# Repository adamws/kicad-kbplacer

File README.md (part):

#  kicad-kbplacer

KiCad plugin for mechanical keyboard design. It features automatic key placement and routing
based on layout descriptions from [Keyboard Layout Editor NG](https://editor.keyboard-tools.xyz)
and [ergogen](https://github.com/ergogen/ergogen).

**Table of Contents**
- [Motivation](#motivation)
- [Features](#features)
- [Installation](#installation)
  - [As KiCad plugin](#installation-as-kicad-plugin)
  - [As python package](#installation-as-python-package)
- [Use from KiCad](#how-to-use-from-kicad)
  - [Options overview](#options-overview)
  - [Diode placement and routing](#diode-placement-and-routing)
    - [Diode automatic orientation adjustment](#diode-automatic-orientation-adjustment)
  - [Track templating](#track-templating)
    - [JSON presets](#json-presets)
  - [Additional elements placement](#additional-elements-placement)
  - [Building board outline](#building-board-outline)
  - [Run without layout](#run-without-layout)
- [Use from CLI or from another tools](#how-to-use-from-cli-or-another-tools)
  - [Run as a script](#run-as-a-script)
  - [Use in python projects](#use-in-python-projects)
- [Demo keyboard project](#demo-keyboard-project)
- [Troubleshooting](#troubleshooting)
  - [Plugin does not load](#plugin-does-not-load)
  - [Plugin misbehaves or crashes](#plugin-misbehaves-or-crashes)

<!-- TOC -->
## Motivation

All PCB's for mechanical keyboards shares common properties which creates great
opportunity for scripting. Although this project does not aim to provide
complete automatic PCB generation tool it speeds up development process
by reducing tedious element placement and routing tasks.

<!-- TOC -->
## Features

- Automatic keys and diodes placement
- Track routing and track template replication
- Support for KLE, [VIA](https://www.caniusevia.com/docs/layouts), [QMK](https://docs.qmk.fm/reference_info_json#layouts) and [ergogen](https://github.com/ergogen/ergogen) inputs
- User selectable diode position in relation to key position
- Configurable additional elements placement
- Board outline generation

> [!NOTE]
> KLE is a layout description format established by https://github.com/ijprest
> and used by https://www.keyboard-layout-editor.com/
>
> The [Keyboard Layout Editor NG](https://editor.keyboard-tools.xyz/) referenced in
> this documentation is a modernized re-implementation using same data format.

> [!WARNING]
> Ergogen support is new experimental feature and it has not been tested extensively

Some examples can be found in [examples](./examples) directory.

**See also:**

:link: [Keyboard PCB design with ergogen and kbplacer](https://adamws.github.io/keyboard-pcb-design-with-ergogen-and-kbplacer/)

<!-- TOC -->
## Installation

<!-- TOC -->
### As KiCad plugin

To install release version of this plugin, use KiCad's `Plugin and Content Manager`
and select `Keyboard footprints placer` from official plugin repository.

To install development version, see how to use [custom plugin repository](./docs/custom_repository.md).
Custom repository is automatically updated with latest `master` branch builds
and it is available [here](https://adamws.github.io/kicad-kbplacer).

For development activities, it is recommended to checkout this repository and copy (or link)
content of `kbplacer` directory to one of the KiCad's plugin search paths.
For more details see [this](https://dev-docs.kicad.org/en/apis-and-binding/pcbnew/) guide.

After installation, plugin can be started by clicking plugin icon on the toolbar:

or selecting it from `Tools -> External Plugins` menu.
For more details about plugin usage see [Use from KiCad](#how-to-use-from-kicad) section.

<!-- TOC -->
### As python package

The `kbplacer` can be installed with pip:

```shell
pip install kbplacer
```

When installed this way, it **can't** be launched from KiCad as KiCad plugin.
This option exist for usage via command line interface or for integrating with
another tools.

Command line interface provides more options but generally it is recommended for
more advanced users. For example it allows to create PCBs without schematic,
which is non-typical KiCad workflow.
For details see [Use from CLI or from another tools](#how-to-use-from-cli-or-another-tools) section.

> [!IMPORTANT]
> Most of the `kbplacer` python package functionalities depends on `pcbnew` package
> which is distributed as part of KiCad installation.
> This means, that on Windows it is **required** to use python bundled with KiCad.
> On Linux, `pcbnew` package should be available globally (this can be verified by
> running `python -c "import pcbnew; print(pcbnew.Version())"`) so it may not work
> inside isolated environment. To install inside virtual environment created with `venv`
> it is required to use `--system-site-package` option when creating this environment.

> [!NOTE]
> Both installation methods can be used simultaneously. When installed as KiCad plugin,
> some scripting capabilities are still available, but in order to use `kbplacer`
> in another python scripts, installing as python package is required.

<!-- TOC -->
## Use from KiCad

This is _traditional_ way of using this tool. Before it can be used on `kicad_pcb` project
file, user needs to create it and populate with footprints. In typical KiCad workflow
this is started by creating schematic. When PCB file is ready, user can start `kbplacer`
plugin in GUI mode from KiCad and run it with selected options.
To use this tool in this way, it needs to be installed following [plugin installation guide](#as-kicad-plugin).

- Create switch matrix schematic which meets following requirements:
  - Each switch has connected diode
    - Diodes can be connected in either direction. Track router attempts to connect
      closest (to each other) pads of switch and diode as long as both have same `netname`,
      i.e. are connected on the schematic
    - Each switch can have multiple diodes
  - Symbols are ordered by Y position.
      - :warning: This annotation scheme might not work well for certain 'ergo' layouts.
      - Annotation order is ignored when using layout with mapping to matrix defined
        (see [VIA](https://www.caniusevia.com/docs/layouts#switch-matrix-co-ordinates)
        specification).

    To learn more see [annotation guide](./docs/annotation_guide.md).

- Create new PCB and load netlist
- Obtain json layout file from [Keyboard Layout Editor NG](https://editor.keyboard-tools.xyz) or
  convert [ergogen](https://github.com/ergogen/ergogen) points file to json

  <details>
  <summary>Keyboard Layout Editor NG details <i>(click to expand)</i></summary>

    Plugin supports both raw and internal [kle-serial](https://github.com/ijprest/kle-serial) layout files
    and [via](https://www.caniusevia.com/docs/layouts) files.
    Detection of layout format will be done automatically.

    > [!NOTE]
    > When using `via` layouts, switch matrix **must** be annotated according to `via` rules.
    > If layout supports [multiple layout of keys](https://www.caniusevia.com/docs/layouts#layout-options)
    > only the default one will be used by `kicad-kbplacer`.

  </details>

  <details>
  <summary>ergogen details <i>(click to expand)</i></summary>

    - open your design in https://ergogen.xyz/ and enable `Debug` in options

    - download `points.yaml`

    - convert `yaml` to `json` (this operation is not integrated with `kicad-kbplacer` source
      because it would require installation of third-party `pyyaml` package and there is no
      good way to manage plugin dependencies yet)
      - you can use online converter, for example https://jsonformatter.org/yaml-to-json
    - converted file should be automatically recognized in next steps

  </details>

- Run `kicad-kbplacer` plugin
- Select json layout file and plugin options and click OK.

It is possible to run this plugin from command line. Everything which can be done via GUI can
be also achieved using command line.
Execute following command (in the directory where plugin is installed) to get more details:

```
python -m com_github_adamws_kicad-kbplacer --help
```

> [!IMPORTANT]
> On windows, use python bundled with KiCad

<!-- TOC -->
### Options overview

<table>
  <tr>
    <th align="center"><b>Section</b></th>
    <th align="center"><b>Label</b></th>
    <th align="center"><b>Description</b></th>
  </tr>
  <tr>
    <td rowspan="6" align="center" style="vertical-align: middle;">Switch settings</td>
    <td align="center" style="vertical-align: middle;">Keyboard Layout</td>
    <td>
      Layout file path or <a href="https://editor.keyboard-tools.xyz/">Keyboard Layout Editor NG</a>
      share link (<code>https://editor.keyboard-tools.xyz/#share=...</code>).
      Supports Keyboard Layout Editor NG
      json layouts in both raw and internal form, <a href="https://www.caniusevia.com/docs/layouts">via</a>
      and <a href="https://docs.qmk.fm/reference_info_json#layouts">qmk</a> json layouts and <a href="https://docs.ergogen.xyz/formats">ergogen</a>
      canonical yaml points files converted to json.</br>
      Can be empty to run without switch footprints placement.
    </td>
  </tr>
  <tr>
    <td align="center" style="vertical-align: middle;">Step X / Step Y</td>
    <td>
      Distance (in millimeters) of 1U between two switches in X and Y directions
      (defaults to <code>19.05</code>).</br>
      When selected layout file explicitly defines spacing in its metadata,
      these fields are updated with values from that file.
    </td>
  </tr>
  <tr>
    <td align="center" style="vertical-align: middle;">Footprint Annotation</td>
    <td>
      The switch footprint annotation format with single replacement field <code>{}</code>
      which will get replaced with incremented footprint number.
      This string is internally used by python's <code>str.format</code> function.
    </td>
  </tr>
  <tr>
    <td align="center" style="vertical-align: middle;">Start index</td>
    <td>
      Starting index used to match footprint annotations (default: 1).
      Controls which number to use when matching the first switch footprint.
      For example, with annotation format <code>SW{}</code> and start index <code>0</code>,
      the first switch will be <code>SW0</code> instead of <code>SW1</code>.
    </td>
  </tr>
  <tr>
    <td align="center" style="vertical-align: middle;">Orientation</td>
    <td>
      Angle (in degrees) of switch footprints.
    </td>
  </tr>
  <tr>
    <td align="center" style="vertical-align: middle;">Side</td>
    <td>
      Selects <code>Front</code> or <code>Back</code> side of the board.
    </td>
  </tr>
  <tr>
    <td rowspan="9" align="center" style="vertical-align: middle;">Switch diodes settings</td>
    <td align="center" style="vertical-align: middle;">Allow autoplacement</td>
    <td>
      Enables automatic diodes positioning. When turned on, each diode will be placed
      next to the switch footprint with common net, according to the position
      settings. When disabled, diodes will not be moved.</br>
      If any switch has more than one diode, then <code>Default</code> and <code>Custom</code>
      position options are not supported.
    </td>
  </tr>
  <tr>
    <td align="center" style="vertical-align: middle;">Route with switches</td>
    <td>
      Enables automatic routing of switch-diode pairs. If user manually route first pair,
      then it replicates the connection for remaining pairs. If not, uses automatic
      internal router. When automatic router used, attempts to connect only two closest
      pads of the same net. Automatic router will use default track width of a routed netclass.
    </td>
  </tr>
  <tr>
    <td align="center" style="vertical-align: middle;">Automatically adjust orientation</td>
    <td>
      Enables automatic diode orientation adjustment based on distance between diode
      and corresponding switch. Useful for some key matrix types, for example Japanese
      duplex matrix, where diodes are connected with alternating directions.
    </td>
  </tr>
  <tr>
    <td align="center" style="vertical-align: middle;">Footprint annotation</td>
    <td>
      The diode annotation format. Same rules as for switch footprint annotation applies.
    </td>
  </tr>
  <tr>
    <td align="center" style="vertical-align: middle;">Position</td>
    <td>
      Diode position option with four possible choices:<br>
      &emsp;<code>Default</code> - positions diodes to default position<br>
      &emsp;<code>Custom</code> - positions diodes based on user defined values<br>
      &emsp;<code>Relative</code> - uses first switch-diode pair to get relative position
      between them and uses that as reference position for remaining pairs<br>
      &emsp;<code>Preset</code> - uses provided <code>kicad_pcb</code> template
      or JSON preset file to get relative position and tracks for replication for all
      switch-diode pairs
    </td>
  </tr>
  <tr>
    <td align="center" style="vertical-align: middle;">Offset X/Y</td>
    <td>
      Distance (in millimeters) from the center of switch footprint to the center of diode footprint.
      Accepts floating values with <code>.</code> (dot) decimal separator.</br>
      Applicable only for <code>Custom</code> position option.
    </td>
  </tr>
  <tr>
    <td align="center" style="vertical-align: middle;">Orientation</td>
    <td>
      Angle (in degrees) of diode footprint. If switch is rotated it will be automatically
      adjusted to match switch rotation</br>
      Applicable only for <code>Custom</code> position option.
    </td>
  </tr>
  <tr>
    <td align="center" style="vertical-align: middle;">Side</td>
    <td>
      Selects <code>Front</code> or <code>Back</code> side of the board.</br>
      Applicable only for <code>Custom</code> position option.
    </td>
  </tr>
  <tr>
    <td align="center" style="vertical-align: middle;">Load from</br>/</br>Save to</td>
    <td>
      The preset <code>kicad_pcb</code> or <code>json</code> file path to use when position option is equal <code>Preset</code>
      or optional file path to store current position and tracks when position option
      is equal <code>Relative</code>.
    </td>
  </tr>
  <tr>
    <td align="center" style="vertical-align: middle;">Additional elements settings</td>
    <td align="center" style="vertical-align: middle;">-</td>
    <td>
      This is equivalent of <b>Switch diodes settings</b> section with these exceptions:</br>
      1) It is possible to add/subtract elements from the list using <code>+/-</code> buttons</br>
      2) <b>Allow autoplacement</b> option is missing, footprints which should not be moved
      should not be added to the list</br>
      3) Footprints from this sections are not routed
    </td>
  </tr>
  <tr>
    <td rowspan="5" align="center" style="vertical-align: middle;">Other settings</td>
    <td align="center" style="vertical-align: middle;">Route rows and columns</td>
    <td>
      Enables/disables automatic routing of keyboard switch matrix.
      Works by finding all pads with nets matching <code>COL(\d+)</code> and
      <code>ROW(\d+)</code> regular expressions (ignoring case) and connecting them
      using simplified internal router. Configuration of row/column naming scheme
      is not yet supported.
      Automatic router will use default track width of a routed netclass.
    </td>
  </tr>
  <tr>
    <td align="center" style="vertical-align: middle;">Controller circuit template file</td>
    <td>
      Path to <code>kicad_pcb</code> template file which can be used for placing/routing
      repetitive parts of the PCBs. It is expected that user creates own templates.</br>
      This is optional and not very well documented process.
    </td>
  </tr>
  <tr>
    <td align="center" style="vertical-align: middle;">Build board outline</td>
    <td>
      Enables/disables board outline creation based on selected footprints (if any)
      or all switch footprints.</br>
      Using selected footprints is supported only for KiCad 7 or above.
    </td>
  </tr>
  <tr>
    <td align="center" style="vertical-align: middle;">Outline delta</td>
    <td>
      The amount (in millimeters) to inflate/deflate generated outline shape.
    </td>
  </tr>
  <tr>
    <td align="center" style="vertical-align: middle;">Layout offset</td>
    <td>
      The X and Y placement offset for the keyboard layout in millimeters.
      If not specified, offset is auto-calculated to align the first key to a grid
      with an offset to avoid pcbnew's Drawing Sheet borders.
      Uses topmost-leftmost key as the reference.
    </td>
  </tr>
</table>

<!-- TOC -->
### Diode placement and routing

By default diodes are placed like shown below. This placement may not work for all switch and diode
footprints combinations.

Before | After
--- | ---
 | 

To use custom diode position there are two available options. Either select `Custom` in `Position` dropdown
and define `X/Y offset`, `Orientation` and `Front` or `Back` side:

or manually place `D1` diode to desired position in relation to first switch and run plugin with
`Relative` `Position` option selected.

Remaining switch-diode pairs will be placed same as the first one.
To save current template, set `Save to` path. This can be later re-used with `Preset` `Position` option.

Before | After
--- | ---
 | 

Some custom diodes positions may be to difficult for router algorithm.
In the above example it managed to connect diodes to switches but failed to connect diodes together.

Switch-to-diode routing is not done with proper auto-routing algorithm and it is very limited.
It attempts to create track in the shortest way (using 45&deg; angles) and doesn't look for other options
if there is a collision, leaving elements unconnected.

<!-- TOC -->
#### Diode automatic orientation adjustment

Some key matrix types use diodes in alternating directions (see [The (Japanese) duplex matrix](https://kbd.news/The-Japanese-duplex-matrix-1391.html)),
making it undesirable to use a single `Position` value for all of them.
When `Automatically adjust orientation` is enabled, `kicad-kbplacer` will choose between two positions:
the one defined by the `Position` controls values and another with the orientation rotated by 180 degrees.
It then selects the position where the distance between the switch and diode pads is shortest.

Consider following example:

Schematic | Automatic adjustment disabled | Automatic adjustment enabled
--- | --- | ---
 |  | 

<!-- TOC -->
### Track templating

If first switch-diode pair is routed before plugin execution, as shown below, `kicad-kbplacer` instead of
using it's built in routing algorithm, will copy user's track. This allow to circumvent plugin's router
limitations. This is applicable only for `Relative` `Position` option or when diode placement disabled
(with `Allow autoplacement` unticked). The latter is suited mostly for routing boards generated with
`ergogen`. When using `Relative Position` and `Save to` path defined, tracks will be stored in template.
Then it can be re-used when using `Preset` `Position` option.

Before | After
--- | ---
 | 

> [!NOTE]
> Track templating is recommended for more complicated switch footprints, for example reversible kailh.
> When switch footprint has multiple pads with the same net name, automatic router would try to connect
> only the two closest pads between diode and switch.

Below [example](./examples/2x3-rotations-custom-diode-with-track-and-complex-footprint) shows more complicated custom diode position with track template pre-routed by the user.
Manual work needs to be done only for first switch-diode pair, plugin will replicate layout for the
remaining pairs:

> [!WARNING]
> All footprints for diodes and switches **must** have same pad layouts, otherwise connection replication
> may yield unexpected results

After replication `kicad-kbplacer` logs a warning for every switch which template tracks did not connect
with its diodes or which got connected to pads of different nets.

<!-- TOC -->
#### JSON presets

`Preset` `Position` option accepts JSON file in place of `kicad_pcb` template, for example
`--diode "D{} PRESET preset.json"`. This format is meant for tools generating presets
programmatically. It is described by [switch-preset.schema.json](./docs/switch-preset.schema.json):
all coordinates are relative to switch origin (switch at 0&deg; orientation, on the front side),
in integer nanometres, and field names follow KiCad's IPC API types.

Existing `kicad_pcb` template can be converted with:

```shell
python -m kbplacer.connection_preset to-json diode_template.kicad_pcb > preset.json
```

Pad centres, layers and nets of a switch-diode pair placed with `CUSTOM` position, in the same
coordinates, can be printed with:

```shell
python -m kbplacer.pair_pads \
  --switch-footprint /path/Switch_Keyboard_Cherry_MX.pretty:SW_Cherry_MX_PCB_1.00u \
  --diode-footprint /usr/share/kicad/footprints/Diode_SMD.pretty:D_SOD-123F \
  --diode-position "5.08 4 90 BACK"
```

JSON presets can't be used for additional elements, and support only front side switches
(routing fails when any switch is on the back side).
`Preset` position with switch-diode routing can't be combined with diodes orientation adjustment
(`--optimize-diodes-orientation`), because template tracks assume the same diode orientation
for every switch.

<!-- TOC -->
### Additional elements placement

In case additional elements need to be automatically placed next to corresponding switches (for example
stabilizer footprints if not integral part of switch footprint, or RGB LEDs), define entries
in `Additional elements settings` section. It behaves very similarly to switch diodes options with few exceptions:

- corresponding switch is matched based on annotation number and not net code
- there is no default position defined
- there is no track routing

<!-- TOC -->
### Building board outline

The `kicad-kbplacer` plugin is capable of generating board edges around selected footprints
or all switches footprints (matched using `Switch Settings - Annotation Footprint` value).
It uses convex hull algorithm to calculate outline and allows to specify additional
increase/decrease amount by `Outline delta` value.

Outline delta 2.0mm | Outline delta -1.0mm
--- | ---
 | 

> [!IMPORTANT]
> To build outline using selected footprints, selection must be done before launching plugin
> and KiCad 7 or above must be used

<!-- TOC -->
### Run without layout

Creating tracks, placing switch associated elements (like diodes) or building board outline
does not require layout file.
With empty `Keyboard Layout` field, switch placement is simply skipped.
Placing and routing of other elements will use already placed switches as reference points
and won't move them. This might be useful for PCB files generated by other tools,
for example [ergogen](https://github.com/ergogen/ergogen).

This works with custom diode positions and [track templating](#track-templating).

<!-- TOC -->
## Use from CLI or from another tools

<!-- TOC -->
### Run as a script

The `kbplacer` module might be executed as a script using python's `-m` command line option.

```shell
python -m kbplacer
```

This is command line equivalent of running this tool as KiCad plugin but without GUI interface.
Run it with `--help` option to get more details about options and CLI usage.

#### Layout format conversion script

The `kbplacer` is capable of converting layouts between various formats.
For example, to convert ergogen point file to KLE layout file:

```shell
python -m kbplacer.kle_serial \
  --in tests/data/ergogen-layouts/absolem-simple-points.yaml --inform ERGOGEN_INTERNAL \
  --out $(pwd)/absolem-kle.json --outform KLE_RAW
```

This command generates [this](./tests/data/ergogen-layouts/absolem-simple-reference.json) file
which can be loaded by Keyboard Layout Editor NG.
Use `--print-url` to print Keyboard Layout Editor NG link with the layout
(or `--open-editor` to open it in web browser).

In case of VIA-like annotated layouts there is an option to perform 'collapse' operation.

```shell
python -m kbplacer.kle_serial \
  --in tests/data/via-layouts/wt60_d.json --inform KLE_VIA \
  --out $(pwd)/wt60_d-internal-collapsed.json --outform KLE_INTERNAL --collapse
```

<table>
    <tr>
        <td style="width:50%" align="center"><b>Before collapse</b></td>
        <td style="width:50%" align="center"><b>After collapse</b></td>
    </tr>
    <tr>
        <td></td>
        <td></td>
    </tr>
</table>

Layout collapsing moves keys to theirs final physical position and removes
duplicates. Key is considered duplicate when there is another key of same
matrix position and size.

#### KiCad schematic generation script

To generate schematic file and schematic image based on layout file:

```shell
python -m kbplacer --create-sch-file --layout <via-annotated-layout.json> --sch-file output.kicad_sch
kicad-cli sch export svg -e output.kicad_sch
```

Generated schematics are bundled into a KiCad project, i.e. `output.kicad_pro` is
created next to `output.kicad_sch`. The project basename is taken from `--pcb-file`
when given, otherwise from `--sch-file`.

It is also possible to generate an LED chain sheet (`--create-led-sch-file`, requires
KiCad 9.0 or above). When more than one sheet is requested, sheets are tied together
either as separate top-level sheets (`--bundle-strategy flat`, KiCad 10.0 and above)
or with a hierarchical root sheet (`--bundle-strategy hierarchical`). By default,
strategy is selected automatically based on KiCad version.
Run `python -m kbplacer --help` for details.

##### Presets

Layout independent parts of a keyboard (microcontroller circuit, USB connector, ...)
can be added from [KiCad design blocks](https://docs.kicad.org/9.0/en/eeschema/eeschema_design_blocks.html)
with `--preset` (may be repeated). Each preset becomes a schematic sheet of the generated
project and its PCB layout (footprints, tracks, vias, zones) is copied to the board
created with `--create-pcb-file`, grouped and placed below the keyboard or at given
position, on the side of the board given with `FRONT`/`BACK` (the layout is
flipped when the block was designed for the other side):

```shell
python -m kbplacer --create-pcb-file --create-sch-file --pcb-file keyboard.kicad_pcb \
  --layout <via-annotated-layout.json> --switch-footprint ... --diode-footprint ... \
  --preset "mcu_atmega32u4_v1 120 30 90 FRONT"
```

Presets are plain design blocks, editable in KiCad without kbplacer. When added:

- references are renumbered so that they do not collide with each other and with
  the key matrix (e.g. preset `C1` becomes `C43` if LED chain uses `C1`-`C42`),
- global labels `GPIO<n>` mark microcontroller pins available for the key matrix,
  they are renamed to rows and then columns nets, in `GPIO` number order or in the
  order given with `--matrix-pin-order`. Only one preset may expose them,
- other global labels (e.g. `MCU_D+`) are kept, they connect presets with each other.

Presets bundled with kbplacer (`python -m kbplacer --list-presets`) are used by name,
other design blocks by `path/to/library.kicad_blocks:block_name` identifier or
`path/to/block.kicad_block` directory. See [available presets](kbplacer/presets/README.md)
for the list of bundled presets with schematic and PCB previews and how to create new ones.

> [!WARNING]
> This requires installation with optional <code>schematic</code> dependencies:
>
> <code>pip install kbplacer[schematic]</code>

#### Extra tools

The `kbplacer` is used by additional tools available in [tools](tools/README.md) directory.

<table>
    <tr>
        <td style="width:33%" align="center"><b>Tool</b></td>
        <td align="center"><b>Example result</b></td>
    </tr>
    <tr>
        <td><code>layout2image.py</code> - generates KLE-like image for layout</td>
        <td></td>
    </tr>
    <tr>
        <td>
            <code>layout2openscad.py</code> - generate plate for <a href="https://openscad.org/">openscad</a></br>
            (⚠️ experimental)
        </td>
        <td></td>
    </tr>
    <tr>
        <td>
            <code>kle2kle.py</code> - edit KLE layout, supports:</a></br>
            labels and colors reset and automatic VIA style <code>row,column</code> matrix label annotation.
        </td>
        <td></td>
    </tr>
    <tr>
        <td>
            <code>pcb2layout.py</code> - reverse-engineer KLE layout from existing <code>.kicad_pcb</code> file</br>
            (⚠️ experimental)
        </td>
        <td></td>
    </tr>
</table>

<!-- TOC -->
### Use in python projects

Some `kbplacer` functionality might be reused in another projects.
For example, to parse raw KLE data to it's internal form run:

``` python
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
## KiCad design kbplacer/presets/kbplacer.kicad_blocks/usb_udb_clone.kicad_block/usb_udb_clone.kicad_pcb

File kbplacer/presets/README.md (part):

# Presets

Presets are layout independent parts of a keyboard (microcontroller circuit,
USB connector, ...) which `kbplacer` adds to the generated project next to the
key matrix. They are plain [KiCad design blocks](https://docs.kicad.org/10.0/en/eeschema/eeschema_design_blocks.html),
so they can be used and edited in KiCad without `kbplacer`.
They are distributed with `kbplacer` (python package and KiCad plugin) in
`kbplacer.kicad_blocks` library next to this file, add it to KiCad's design
block library table to place them by hand (the [demo project](../../demo/demo.kicad_pro)
already lists it).

Use a preset by its name with `--preset` option (`python -m kbplacer --list-presets`
lists them), it may be repeated to combine presets (for example microcontroller
with USB connector). Design blocks of other libraries are used with
`path/to/library.kicad_blocks:block_name` identifier.

```shell
python -m kbplacer --create-pcb-file --create-sch-file --pcb-file keyboard.kicad_pcb \
  --layout <via-annotated-layout.json> --switch-footprint ... --diode-footprint ... \
  --preset "mcu_atmega32u4_v1 120 30 90 BACK" \
  --preset "usb_udb_clone 120 10 0 BACK"
```

Microcontroller presets connect to USB presets with `MCU_D+`/`MCU_D-` global
labels, power nets (`VCC`, `GND`) are shared by all presets and the key matrix.

The preset schematic becomes a sheet of the generated project and its PCB layout
is placed at the given `X Y [ROTATION]` (mm, degrees) or below the keyboard when
position is omitted. `FRONT` or `BACK` puts its components on that side of the
board (the layout is flipped around the block origin when needed), so any preset
works on either side. Previews below show the components side. References are
renumbered so they do not collide with the key matrix or other presets. See [presets](../../README.md#presets) for details.

To try it, run `just presets` (see [`.justfile`](../../.justfile)).

## Available presets

<!-- presets:begin -->
<!-- generated with tools/block2image.py, do not edit by hand -->

| Preset | Description | Key matrix | PCB |
| --- | --- | --- | --- |
| [mcu_atmega32u4](#mcu_atmega32u4)<br>variants: [mcu_atmega32u4_v1](#mcu_atmega32u4_v1), [mcu_atmega32u4_v2](#mcu_atmega32u4_v2) | ATmega32U4 microcontroller with 16 MHz crystal, reset button, USB data line resistors and decoupling capacitors. | 25 pins, up to 12×13 |   |
| [usb_minimal](#usb_minimal) | USB-C receptacle (USB 2.0) with TPD2S017 ESD protection, connector VBUS powers VCC directly. Minimal version without CC pull-down resistors, only USB-A to USB-C cables power the board. | - |  |
| [usb_udb_clone](#usb_udb_clone) | USB-C receptacle (USB 2.0) with TPD4E05U06DQA ESD protection, CC pull-down resistors, polyfuse and zener diode on VCC. Clone of Unified Daughterboard (UDB-C) circuit, with two-layer routing. USB data lines are 0.1524 mm (6 mil) wide, below default 0.2 mm minimum track width of KiCad design rules. | - |  |

### mcu_atmega32u4

ATmega32U4 microcontroller with 16 MHz crystal, reset button, USB data line resistors and decoupling capacitors.

Keywords: mcu atmega32u4 usb

Variants `mcu_atmega32u4_v1`, `mcu_atmega32u4_v2` share the schematic and differ in PCB layout.

- **Key matrix:** 25 `GPIO` pins, up to 12×13 matrix (156 keys)
- **Interface labels:** `MCU_D+`, `MCU_D-`
- **Power:** `GND`, `VCC`

<details>
<summary>Components (15)</summary>

| References | Value | Footprint |
| --- | --- | --- |
| BTN1 | SW_SPST | `Button_Switch_SMD:SW_SPST_TL3342` |
| C1-C2 | 22p | `Capacitor_SMD:C_0603_1608Metric` |
| C3-C6 | 0.1u | `Capacitor_SMD:C_0603_1608Metric` |
| C7 | 4.7u | `Capacitor_SMD:C_0603_1608Metric` |
| C8 | 1u | `Capacitor_SMD:C_0603_1608Metric` |
| R1-R2 | 22 | `Resistor_SMD:R_0603_1608Metric` |
| R3-R4 | 10k | `Resistor_SMD:R_0603_1608Metric` |
| U1 | ATmega32U4-M | `Package_DFN_QFN:QFN-44-1EP_7x7mm_P0.5mm_EP5.2x5.2mm` |
| Y1 | 16MHz | `Crystal:Crystal_SMD_3225-4Pin_3.2x2.5mm` |

</details>

<details>
<summary>Matrix pins (<code>--matrix-pin-order</code> labels)</summary>

| Label | Pin |
| --- | --- |
| `GPIO0` | U1 pin 8 (PB0) |
| `GPIO1` | U1 pin 9 (PB1) |
| `GPIO2` | U1 pin 10 (PB2) |
| `GPIO3` | U1 pin 11 (PB3) |
| `GPIO4` | U1 pin 28 (PB4) |
| `GPIO5` | U1 pin 29 (PB5) |
| `GPIO6` | U1 pin 30 (PB6) |
| `GPIO7` | U1 pin 12 (PB7) |
| `GPIO8` | U1 pin 31 (PC6) |
| `GPIO9` | U1 pin 32 (PC7) |
| `GPIO10` | U1 pin 18 (PD0) |
| `GPIO11` | U1 pin 19 (PD1) |
| `GPIO12` | U1 pin 20 (PD2) |
| `GPIO13` | U1 pin 21 (PD3) |
| `GPIO14` | U1 pin 25 (PD4) |
| `GPIO15` | U1 pin 22 (PD5) |
| `GPIO16` | U1 pin 26 (PD6) |
| `GPIO17` | U1 pin 27 (PD7) |
| `GPIO18` | U1 pin 41 (PF0) |
| `GPIO19` | U1 pin 40 (PF1) |
| `GPIO20` | U1 pin 39 (PF4) |
| `GPIO21` | U1 pin 38 (PF5) |
| `GPIO22` | U1 pin 37 (PF6) |
| `GPIO23` | U1 pin 36 (PF7) |
| `GPIO24` | U1 pin 1 (PE6) |

</details>

#### mcu_atmega32u4_v1

Elongated layout with USB data lines leaving to the side.

```shell
--preset mcu_atmega32u4_v1
```

- **PCB:** 47.1 × 13.5 mm

#### mcu_atmega32u4_v2

Compact layout with USB data lines leaving to the top.

```shell
--preset mcu_atmega32u4_v2
```

- **PCB:** 32.8 × 22.8 mm

### usb_minimal

USB-C receptacle (USB 2.0) with TPD2S017 ESD protection, connector VBUS powers VCC directly. Minimal version without CC pull-down resistors, only USB-A to USB-C cables power the board.

Keywords: usb usb-c connector esd

```shell
--preset usb_minimal
```

- **PCB:** 9.3 × 11.5 mm

- **Key matrix:** none (no `GPIO<n>` labels)
- **Interface labels:** `MCU_D+`, `MCU_D-`
- **Power:** `GND`, `VCC`

<details>
<summary>Components (2)</summary>

| References | Value | Footprint |
| --- | --- | --- |
| J1 | USB_C_Receptacle_USB2.0_14P | `Connector_USB:USB_C_Receptacle_GCT_USB4105-xx-A_16P_TopMnt_Horizontal` |
| U1 | TPD2S017 | `Package_TO_SOT_SMD:SOT-23-6` |

</details>

### usb_udb_clone

USB-C receptacle (USB 2.0) with TPD4E05U06DQA ESD protection, CC pull-down resistors, polyfuse and zener diode on VCC. Clone of Unified Daughterboard (UDB-C) circuit, with two-layer routing. USB data lines are 0.1524 mm (6 mil) wide, below default 0.2 mm minimum track width of KiCad design rules.

Keywords: usb usb-c connector esd udb

```shell
--preset usb_udb_clone
```

- **PCB:** 13.4 × 14.5 mm

- **Key matrix:** none (no `GPIO<n>` labels)
- **Interface labels:** `MCU_D+`, `MCU_D-`
- **Power:** `GND`, `VCC`

<details>
<summary>Components (6)</summary>

| References | Value | Footprint |
| --- | --- | --- |
| D1 | D_Zener | `Diode_SMD:D_SOD-123` |
| F1 | Polyfuse | `Fuse:Fuse_1206_3216Metric` |
| J1 | USB_C_Receptacle_USB2.0_14P | `Connector_USB:USB_C_Receptacle_HRO_TYPE-C-31-M-12` |
| R1-R2 | 5.1k | `Resistor_SMD:R_0603_1608Metric` |
| U1 | TPD4E05U06DQA | `Package_SON:USON-10_2.5x1.0mm_P0.5mm` |

</details>

<!-- presets:end -->

## Creating presets

1. Open [demo project](../../demo/demo.kicad_pro), its design block library
   table already lists this library as `kbplacer`. Draw the circuit (or place
   an existing preset to modify it), route its PCB and save both as one design
   block to `kbplacer` library (_Save Selection as Design Block_ in schematic
   and PCB editors, under the same block name; to modify a preset, overwrite
   it). Do not save the demo project afterwards, it is the keyboard demo.
   References may differ from the block's original ones, `kbplacer` renumbers
   them anyway.
2. Mark pins which can drive the key matrix with global labels `GPIO0`,
   `GPIO1`, ... `kbplacer` connects them to rows and then columns of the
   matrix in label number order (unless `--matrix-pin-order` used),
   so number them in preferred order. Only one preset may have `GPIO` labels.
3. Connect presets with each other using other global labels, like
   `MCU_D+`/`MCU_D-` of the microcontroller and USB connector.
4. Annotate all symbols, the block PCB must use the same references.
5. Fill the block description (shown in KiCad's design block chooser and below).
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
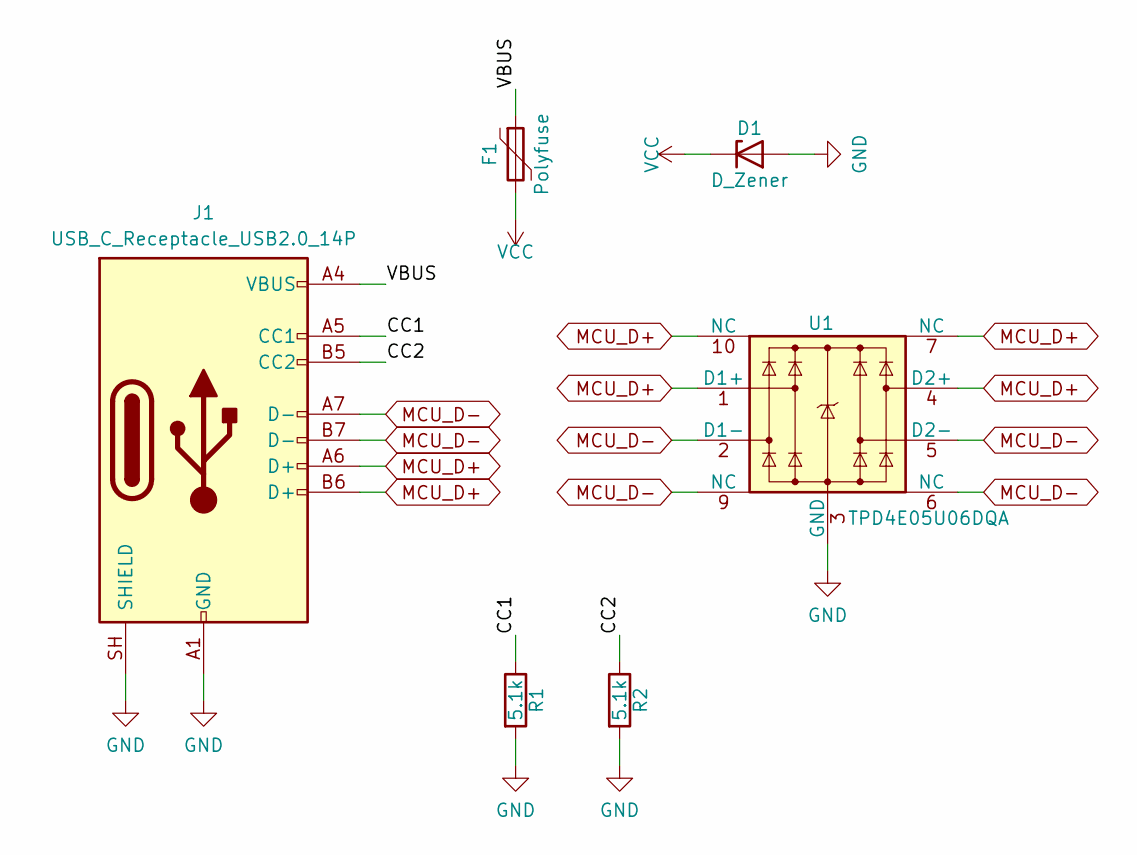
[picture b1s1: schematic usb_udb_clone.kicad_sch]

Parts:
D1: D_Zener; D_SOD-123
F1: Polyfuse; Fuse_1206_3216Metric
J1: USB_C_Receptacle_USB2.0_14P; USB_C_Receptacle_HRO_TYPE-C-31-M-12
R1, R2: 5.1k; R_0603_1608Metric
U1: TPD4E05U06DQA; USON-10_2.5x1.0mm_P0.5mm

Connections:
/CC1: J1.A5 (CC1), R1.1
/CC2: J1.B5 (CC2), R2.1
/VBUS: F1.1, J1.A4 (VBUS), J1.A9 (VBUS), J1.B4 (VBUS), J1.B9 (VBUS)
GND: D1.2 (A), J1.A1 (GND), J1.A12 (GND), J1.B1 (GND), J1.B12 (GND), J1.SH (SHIELD), R1.2, R2.2, U1.3 (GND), U1.8 (GND)
MCU_D+: J1.A6 (D+), J1.B6 (D+), U1.1 (D1+), U1.4 (D2+), U1.7 (NC), U1.10 (NC)
MCU_D-: J1.A7 (D-), J1.B7 (D-), U1.2 (D1-), U1.5 (D2-), U1.6 (NC), U1.9 (NC)
VCC: D1.1 (K), F1.2

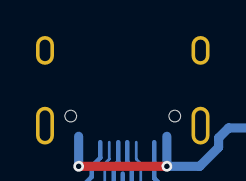
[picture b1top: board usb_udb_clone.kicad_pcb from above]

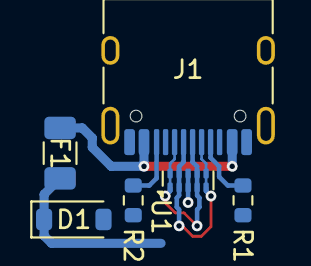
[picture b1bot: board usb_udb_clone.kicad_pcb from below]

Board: 2 copper layers, 6 parts (6 on the bottom side), 7 nets.

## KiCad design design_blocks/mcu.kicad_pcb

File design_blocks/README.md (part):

# Presets

Presets are layout independent parts of a keyboard (microcontroller circuit,
USB connector, ...) which `kbplacer` adds to the generated project next to the
key matrix. They are plain [KiCad design blocks](https://docs.kicad.org/10.0/en/eeschema/eeschema_design_blocks.html),
so they can be used and edited in KiCad without `kbplacer`.
Add `design_blocks/kbplacer.kicad_blocks` to KiCad's design block library table
to place them by hand.

Use a preset with `--preset` option, it may be repeated to combine presets
(for example microcontroller with USB connector):

```shell
python -m kbplacer --create-pcb-file --create-sch-file --pcb-file keyboard.kicad_pcb \
  --layout <via-annotated-layout.json> --switch-footprint ... --diode-footprint ... \
  --preset "design_blocks/kbplacer.kicad_blocks:mcu_atmega32u4_v1 120 30 90 BACK" \
  --preset "design_blocks/kbplacer.kicad_blocks:usb_udb_clone 120 10 0 BACK"
```

Microcontroller presets connect to USB presets with `MCU_D+`/`MCU_D-` global
labels, power nets (`VCC`, `GND`) are shared by all presets and the key matrix.

The preset schematic becomes a sheet of the generated project and its PCB layout
is placed at the given `X Y [ROTATION]` (mm, degrees) or below the keyboard when
position is omitted. `FRONT` or `BACK` puts its components on that side of the
board (the layout is flipped around the block origin when needed), so any preset
works on either side. Previews below show the components side. References are
renumbered so they do not collide with the key matrix or other presets. See [presets](../README.md#presets) for details.

To try it, run `just presets` (see [`.justfile`](../.justfile)).

## Available presets

<!-- presets:begin -->
<!-- generated with tools/block2image.py, do not edit by hand -->

| Preset | Description | Key matrix | PCB |
| --- | --- | --- | --- |
| [mcu_atmega32u4](#mcu_atmega32u4)<br>variants: [mcu_atmega32u4_v1](#mcu_atmega32u4_v1), [mcu_atmega32u4_v2](#mcu_atmega32u4_v2) | ATmega32U4 microcontroller with 16 MHz crystal, reset button, USB data line resistors and decoupling capacitors. | 25 pins, up to 12×13 |   |
| [usb_minimal](#usb_minimal) | USB-C receptacle (USB 2.0) with TPD2S017 ESD protection, connector VBUS powers VCC directly. Minimal version without CC pull-down resistors, only USB-A to USB-C cables power the board. | - |  |
| [usb_udb_clone](#usb_udb_clone) | USB-C receptacle (USB 2.0) with TPD4E05U06DQA ESD protection, CC pull-down resistors, polyfuse and zener diode on VCC. Clone of Unified Daughterboard (UDB-C) circuit, with two-layer routing. | - |  |

### mcu_atmega32u4

ATmega32U4 microcontroller with 16 MHz crystal, reset button, USB data line resistors and decoupling capacitors.

Keywords: mcu atmega32u4 usb

Variants `mcu_atmega32u4_v1`, `mcu_atmega32u4_v2` share the schematic and differ in PCB layout.

- **Key matrix:** 25 `GPIO` pins, up to 12×13 matrix (156 keys)
- **Interface labels:** `MCU_D+`, `MCU_D-`
- **Power:** `GND`, `VCC`

<details>
<summary>Components (15)</summary>

| References | Value | Footprint |
| --- | --- | --- |
| BTN1 | SW_SPST | `Button_Switch_SMD:SW_SPST_TL3342` |
| C1-C2 | 22p | `Capacitor_SMD:C_0603_1608Metric` |
| C3-C6 | 0.1u | `Capacitor_SMD:C_0603_1608Metric` |
| C7 | 4.7u | `Capacitor_SMD:C_0603_1608Metric` |
| C8 | 1u | `Capacitor_SMD:C_0603_1608Metric` |
| R1-R2 | 22 | `Resistor_SMD:R_0603_1608Metric` |
| R3-R4 | 10k | `Resistor_SMD:R_0603_1608Metric` |
| U1 | ATmega32U4-M | `Package_DFN_QFN:QFN-44-1EP_7x7mm_P0.5mm_EP5.2x5.2mm` |
| Y1 | 16MHz | `Crystal:Crystal_SMD_3225-4Pin_3.2x2.5mm` |

</details>

<details>
<summary>Matrix pins (<code>--matrix-pin-order</code> labels)</summary>

| Label | Pin |
| --- | --- |
| `GPIO0` | U1 pin 8 (PB0) |
| `GPIO1` | U1 pin 9 (PB1) |
| `GPIO2` | U1 pin 10 (PB2) |
| `GPIO3` | U1 pin 11 (PB3) |
| `GPIO4` | U1 pin 28 (PB4) |
| `GPIO5` | U1 pin 29 (PB5) |
| `GPIO6` | U1 pin 30 (PB6) |
| `GPIO7` | U1 pin 12 (PB7) |
| `GPIO8` | U1 pin 31 (PC6) |
| `GPIO9` | U1 pin 32 (PC7) |
| `GPIO10` | U1 pin 18 (PD0) |
| `GPIO11` | U1 pin 19 (PD1) |
| `GPIO12` | U1 pin 20 (PD2) |
| `GPIO13` | U1 pin 21 (PD3) |
| `GPIO14` | U1 pin 25 (PD4) |
| `GPIO15` | U1 pin 22 (PD5) |
| `GPIO16` | U1 pin 26 (PD6) |
| `GPIO17` | U1 pin 27 (PD7) |
| `GPIO18` | U1 pin 41 (PF0) |
| `GPIO19` | U1 pin 40 (PF1) |
| `GPIO20` | U1 pin 39 (PF4) |
| `GPIO21` | U1 pin 38 (PF5) |
| `GPIO22` | U1 pin 37 (PF6) |
| `GPIO23` | U1 pin 36 (PF7) |
| `GPIO24` | U1 pin 1 (PE6) |

</details>

#### mcu_atmega32u4_v1

Elongated layout with USB data lines leaving to the side.

```shell
--preset design_blocks/kbplacer.kicad_blocks:mcu_atmega32u4_v1
```

- **PCB:** 47.1 × 13.5 mm

#### mcu_atmega32u4_v2

Compact layout with USB data lines leaving to the top.

```shell
--preset design_blocks/kbplacer.kicad_blocks:mcu_atmega32u4_v2
```

- **PCB:** 32.8 × 22.8 mm

### usb_minimal

USB-C receptacle (USB 2.0) with TPD2S017 ESD protection, connector VBUS powers VCC directly. Minimal version without CC pull-down resistors, only USB-A to USB-C cables power the board.

Keywords: usb usb-c connector esd

```shell
--preset design_blocks/kbplacer.kicad_blocks:usb_minimal
```

- **PCB:** 9.3 × 11.5 mm

- **Key matrix:** none (no `GPIO<n>` labels)
- **Interface labels:** `MCU_D+`, `MCU_D-`
- **Power:** `GND`, `VCC`

<details>
<summary>Components (2)</summary>

| References | Value | Footprint |
| --- | --- | --- |
| J1 | USB_C_Receptacle_USB2.0_14P | `Connector_USB:USB_C_Receptacle_GCT_USB4105-xx-A_16P_TopMnt_Horizontal` |
| U1 | TPD2S017 | `Package_TO_SOT_SMD:SOT-23-6` |

</details>

### usb_udb_clone

USB-C receptacle (USB 2.0) with TPD4E05U06DQA ESD protection, CC pull-down resistors, polyfuse and zener diode on VCC. Clone of Unified Daughterboard (UDB-C) circuit, with two-layer routing.

Keywords: usb usb-c connector esd udb

```shell
--preset design_blocks/kbplacer.kicad_blocks:usb_udb_clone
```

- **PCB:** 13.4 × 14.5 mm

- **Key matrix:** none (no `GPIO<n>` labels)
- **Interface labels:** `MCU_D+`, `MCU_D-`
- **Power:** `GND`, `VCC`

<details>
<summary>Components (6)</summary>

| References | Value | Footprint |
| --- | --- | --- |
| D1 | D_Zener | `Diode_SMD:D_SOD-123` |
| F1 | Polyfuse | `Fuse:Fuse_1206_3216Metric` |
| J1 | USB_C_Receptacle_USB2.0_14P | `Connector_USB:USB_C_Receptacle_HRO_TYPE-C-31-M-12` |
| R1-R2 | 5.1k | `Resistor_SMD:R_0603_1608Metric` |
| U1 | TPD4E05U06DQA | `Package_SON:USON-10_2.5x1.0mm_P0.5mm` |

</details>

<!-- presets:end -->

## Creating presets

1. Draw the circuit in KiCad project (like [`mcu.kicad_sch`](mcu.kicad_sch)
   or [`usb.kicad_sch`](usb.kicad_sch), which holds both USB circuits, each
   PCB layout in a group named like its block), route its PCB and save both
   as one design block to `kbplacer.kicad_blocks` (_Save Selection as Design
   Block_ in schematic and PCB editors, under the same block name).
   References in the project may differ from the block, `kbplacer` renumbers
   them anyway.
2. Mark pins which can drive the key matrix with global labels `GPIO0`,
   `GPIO1`, ... `kbplacer` connects them to rows and then columns of the
   matrix in label number order (unless `--matrix-pin-order` used),
   so number them in preferred order. Only one preset may have `GPIO` labels.
3. Connect presets with each other using other global labels, like
   `MCU_D+`/`MCU_D-` of the microcontroller and USB connector.
4. Annotate all symbols, the block PCB must use the same references.
5. Fill the block description (shown in KiCad's design block chooser and below).
   Alternative PCB layouts of the same circuit are variants: name them
   `<name>_v1`, `<name>_v2`, ... and keep their schematics equal, they are
   presented together with the shared circuit described once. Start variant
   descriptions with the same sentences describing the circuit, the rest
   describes the layout.
6. Regenerate images and the list above:

   ```shell
   just tools-block2image
   # or directly, with KiCad 10.0+ installed:
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
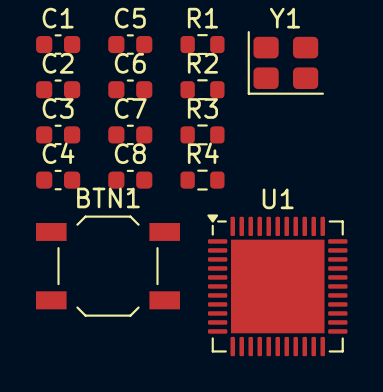
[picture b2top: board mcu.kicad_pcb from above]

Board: 2 copper layers, 15 parts (0 on the bottom side), 9 nets, no tracks yet.

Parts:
BTN1: SW_SPST; SW_SPST_TL3342
C1, C2: 22p; C_0603_1608Metric
C3, C4, C5, C6: 0.1u; C_0603_1608Metric
C7: 4.7u; C_0603_1608Metric
C8: 1u; C_0603_1608Metric
R1, R2: 22; R_0603_1608Metric
R3, R4: 10k; R_0603_1608Metric
U1: ATmega32U4-M; QFN-44-1EP_7x7mm_P0.5mm_EP5.2x5.2mm
Y1: 16MHz; Crystal_SMD_3225-4Pin_3.2x2.5mm

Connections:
/XTAL1: C1.1, U1.17 (XTAL1), Y1.1
/XTAL2: C2.1, U1.16 (XTAL2), Y1.3
GND: BTN1.1 (A), C1.2, C2.2, C3.2, C4.2, C5.2, C6.2, C7.2, C8.2, R3.2, U1.5 (UGND), U1.15 (GND), U1.23 (GND), U1.35 (GND), U1.43 (GND), U1.45 (GND), Y1.2 (G), Y1.4 (G)
unnamed: BTN1.2 (B), R4.1, U1.13 (~RESET)
unnamed: R2.1, U1.4 (D+)
unnamed: R1.1, U1.3 (D-)
unnamed: C8.1, U1.6 (UCAP)
unnamed: R3.1, U1.33 (~HWB/PE2)
VCC: C3.1, C4.1, C5.1, C6.1, C7.1, R4.2, U1.2 (UVCC), U1.7 (VBUS), U1.14 (VCC), U1.24 (AVCC), U1.34 (VCC), U1.44 (AVCC)

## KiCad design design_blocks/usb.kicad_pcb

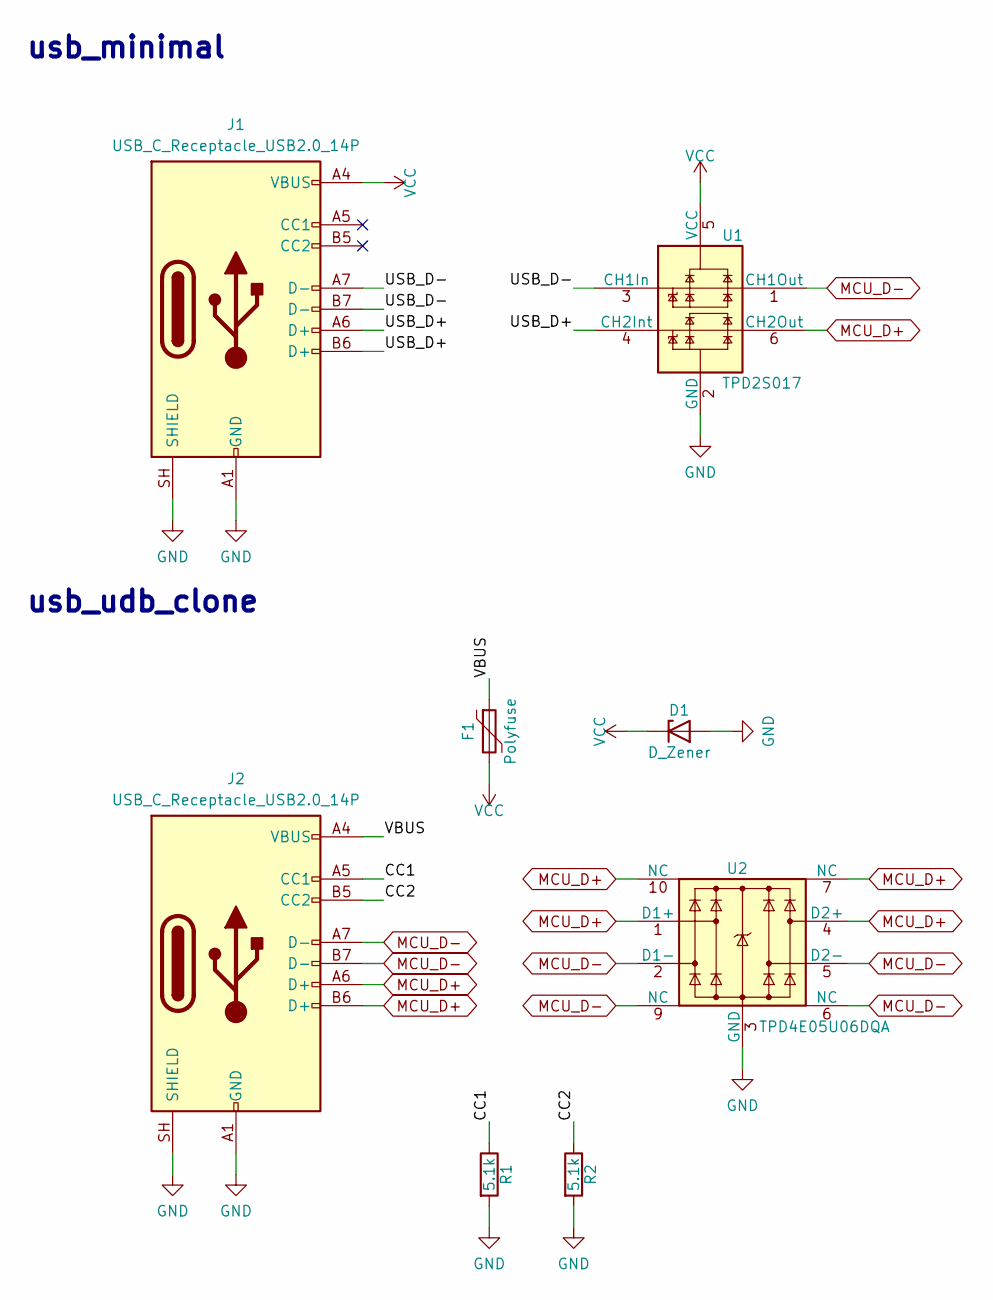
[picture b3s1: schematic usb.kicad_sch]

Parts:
D1: D_Zener; D_SOD-123
F1: Polyfuse; Fuse_1206_3216Metric
J1: USB_C_Receptacle_USB2.0_14P; USB_C_Receptacle_GCT_USB4105-xx-A_16P_TopMnt_Horizontal
J2: USB_C_Receptacle_USB2.0_14P; USB_C_Receptacle_HRO_TYPE-C-31-M-12
R1, R2: 5.1k; R_0603_1608Metric
U1: TPD2S017; SOT-23-6
U2: TPD4E05U06DQA; USON-10_2.5x1.0mm_P0.5mm

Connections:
/CC1: J2.A5 (CC1), R1.1
/CC2: J2.B5 (CC2), R2.1
/USB_D+: J1.A6 (D+), J1.B6 (D+), U1.4 (CH2Int)
/USB_D-: J1.A7 (D-), J1.B7 (D-), U1.3 (CH1In)
/VBUS: F1.1, J2.A4 (VBUS), J2.A9 (VBUS), J2.B4 (VBUS), J2.B9 (VBUS)
GND: D1.2 (A), J1.A1 (GND), J1.A12 (GND), J1.B1 (GND), J1.B12 (GND), J1.SH (SHIELD), J2.A1 (GND), J2.A12 (GND), J2.B1 (GND), J2.B12 (GND), J2.SH (SHIELD), R1.2, R2.2, U1.2 (GND), U2.3 (GND), U2.8 (GND)
MCU_D+: J2.A6 (D+), J2.B6 (D+), U1.6 (CH2Out), U2.1 (D1+), U2.4 (D2+), U2.7 (NC), U2.10 (NC)
MCU_D-: J2.A7 (D-), J2.B7 (D-), U1.1 (CH1Out), U2.2 (D1-), U2.5 (D2-), U2.6 (NC), U2.9 (NC)
VCC: D1.1 (K), F1.2, J1.A4 (VBUS), J1.A9 (VBUS), J1.B4 (VBUS), J1.B9 (VBUS), U1.5 (VCC)

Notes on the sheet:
usb_minimal
usb_udb_clone

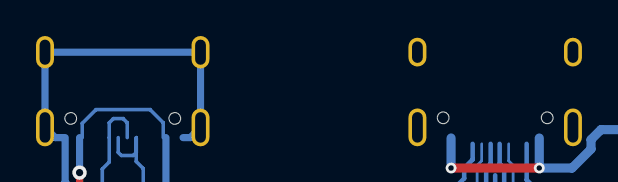
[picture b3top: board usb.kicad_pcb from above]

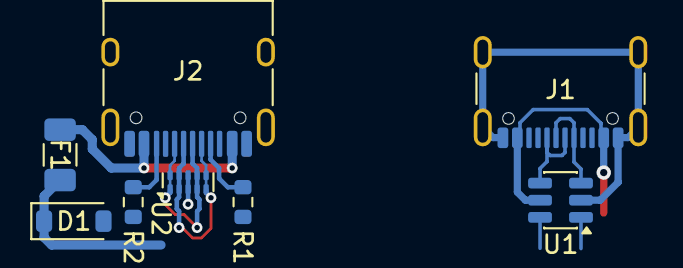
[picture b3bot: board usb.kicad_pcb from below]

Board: 2 copper layers, 8 parts (8 on the bottom side), 9 nets.

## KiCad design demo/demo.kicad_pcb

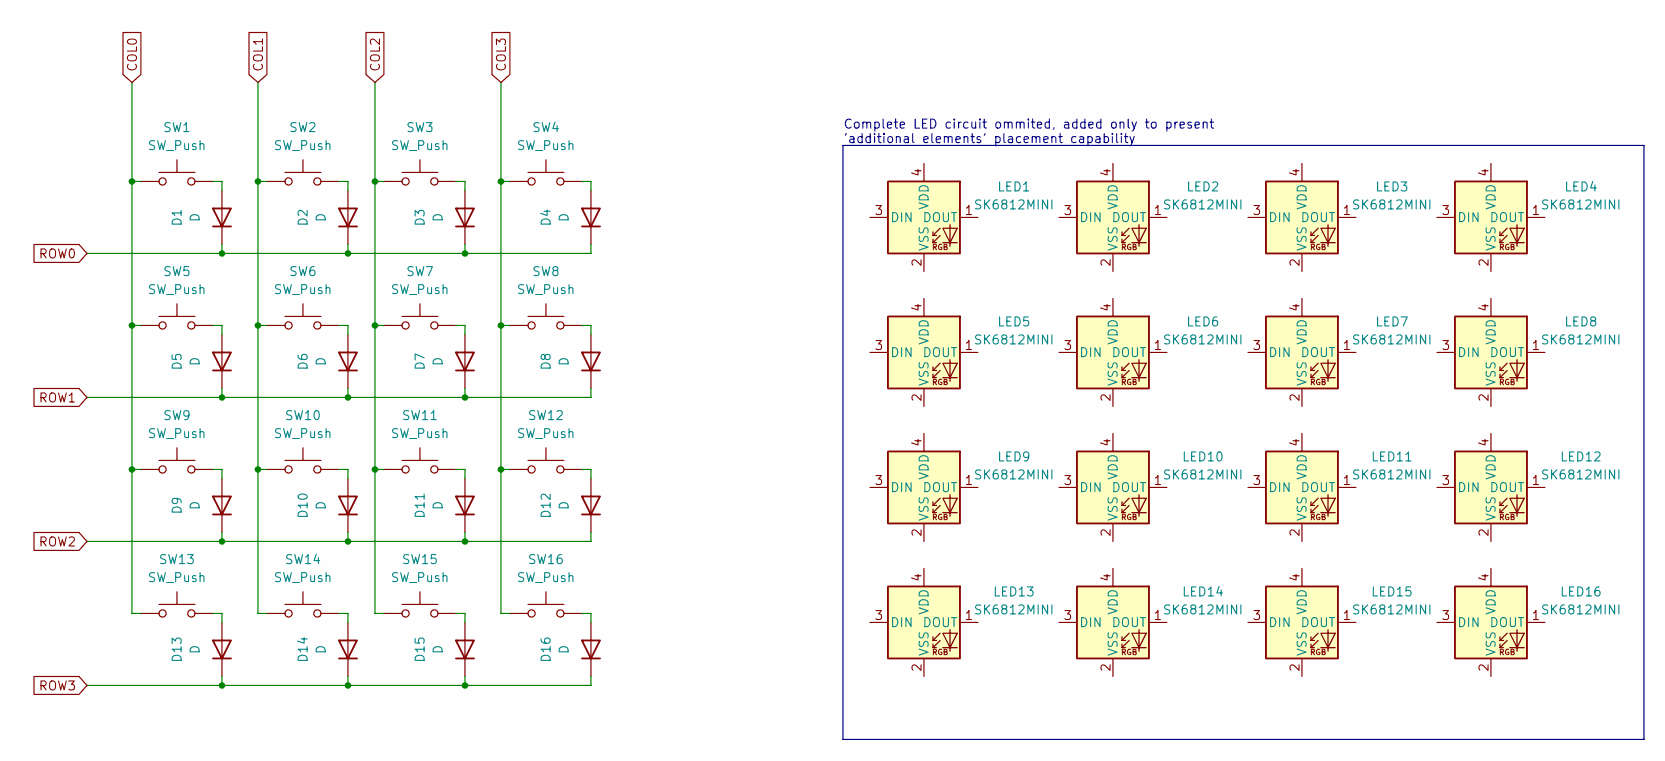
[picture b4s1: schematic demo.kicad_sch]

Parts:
D1, D2, D3, D4, D5, D6, D7, D8, D9, D10, D11, D12, D13, D14, D15, D16: D; D_SOD-323F
LED1, LED2, LED3, LED4, LED5, LED6, LED7, LED8, LED9, LED10, LED11, LED12, LED13, LED14, LED15, LED16: SK6812MINI; LED_SK6812MINI_PLCC4_3.5x3.5mm_P1.75mm
SW1, SW2, SW3, SW4, SW5, SW6, SW7, SW8, SW9, SW10, SW11, SW12, SW13, SW14, SW15, SW16: SW_Push; SW_Cherry_MX_PCB_1.00u

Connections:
COL0: SW1.1, SW5.1, SW9.1, SW13.1
COL1: SW2.1, SW6.1, SW10.1, SW14.1
COL2: SW3.1, SW7.1, SW11.1, SW15.1
COL3: SW4.1, SW8.1, SW12.1, SW16.1
unnamed: D1.2 (A), SW1.2
unnamed: D2.2 (A), SW2.2
unnamed: D3.2 (A), SW3.2
unnamed: D4.2 (A), SW4.2
unnamed: D5.2 (A), SW5.2
unnamed: D6.2 (A), SW6.2
unnamed: D7.2 (A), SW7.2
unnamed: D8.2 (A), SW8.2
unnamed: D9.2 (A), SW9.2
unnamed: D10.2 (A), SW10.2
unnamed: D11.2 (A), SW11.2
unnamed: D12.2 (A), SW12.2
unnamed: D13.2 (A), SW13.2
unnamed: D14.2 (A), SW14.2
unnamed: D15.2 (A), SW15.2
unnamed: D16.2 (A), SW16.2
ROW0: D1.1 (K), D2.1 (K), D3.1 (K), D4.1 (K)
ROW1: D5.1 (K), D6.1 (K), D7.1 (K), D8.1 (K)
ROW2: D9.1 (K), D10.1 (K), D11.1 (K), D12.1 (K)
ROW3: D13.1 (K), D14.1 (K), D15.1 (K), D16.1 (K)

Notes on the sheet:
Complete LED circuit ommited, added only to present 'additional elements' placement capability

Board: 2 copper layers, 48 parts (0 on the bottom side), 24 nets, no tracks yet.

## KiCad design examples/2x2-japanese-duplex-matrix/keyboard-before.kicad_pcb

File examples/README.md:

# Examples

Each example has own directory with following file structure:

- `kle.json` - keyboard's layout downloaded from [Keyboard Layout Editor NG](https://editor.keyboard-tools.xyz/).
- `kle-internal.json` - keyboard's layout after processing with [kle-serial](https://github.com/ijprest/kle-serial).
  This file is also supported by `kbplacer` plugin.
- `keyboard.net` - example's netlist.
- `keyboard-before.kicad_pcb` - PCB file with loaded netlist and parts placed
  at default location (by KiCad's netlist loader). This file is useful for manual
  testing of plugin's code changes.
- `keyboard-after.kicad_pcb` - PCB file after running plugin. Demonstrates
  current capabilities - this file does not contain any manual changes.
- `fp-lib-table` - footprints location file, points to external footprints
  stored in parent's `examples.pretty` directory.
- `keyboard-layout.png` - picture of layout.
- `render.svg` - picture of PCB, this file is created by KiCad's SVG export.

## Examples summary

| Name                                                                         | Keyboard layout                                                                                                                                          | PCB result                                                                                                                                                                                                                                                                                                                                       |
| ---                                                                          | ---                                                                                                                                                      | ---                                                                                                                                                                                                                                                                                                                                              |
| 2x2                                                                          |                                                                                                                  |                                                                                                                                                                                                                                                                                                                    |
| 3x2-sizes                                                                    |                                                                                                      |  Note that in this example `SW2` belongs to column 1 and `SW4&SW6` to column 2.                                                                                                                                                                                                                        |
| 1x4-rotations-90-step                                                        |                                                                              |  Not all diodes are connected together.                                                                                                                                                                                                                                        |
| 2x3-rotations                                                                |                                                                                              |  Diodes `D4` and `D5` are connected because they use same rotation. Elements with different rotation, like `D3` and `D4` are not routed. Placement is ok but some traces need to be added manually.                                                                                            |
| 2x3-rotations with custom diode                                              |                                              |  Same as previous example but with custom diode location and pre-routed track. This custom diode position would not work with automatic switch-diode routing algorithm implemented by the plugin.                                              |
| 2x3-rotations with custom diode and reversible hot swappable kailh footprint |  |  Same as previous example but with custom diode location and pre-routed tracks. Note that this footprint has multiple pads of the same nets. Track template from `SW1` was copied for all of them. |
| 2x3-rotations with two diodes per switch                                     |                                                                         |  Same as `2x3-rotations` example but with two diodes with pre-routed tracks per switch. Note that diodes annotation number does not match switch numbers. Diodes are associated with switches based on netlist.                                                    |
| 2x2 with alternative layout                                                  |                                                                         |  Same as `2x2` example but alternative bottom row `SW3a` key.                                                                                                                                                                                                      |
| 2x2 japanese duplex matrix                                                   |                                                                    |  Same as `2x2` example but with single column and `D2`/`D4` diodes rotated (with `Automatically adjust orientation` option enabled.                                                                                                                           |

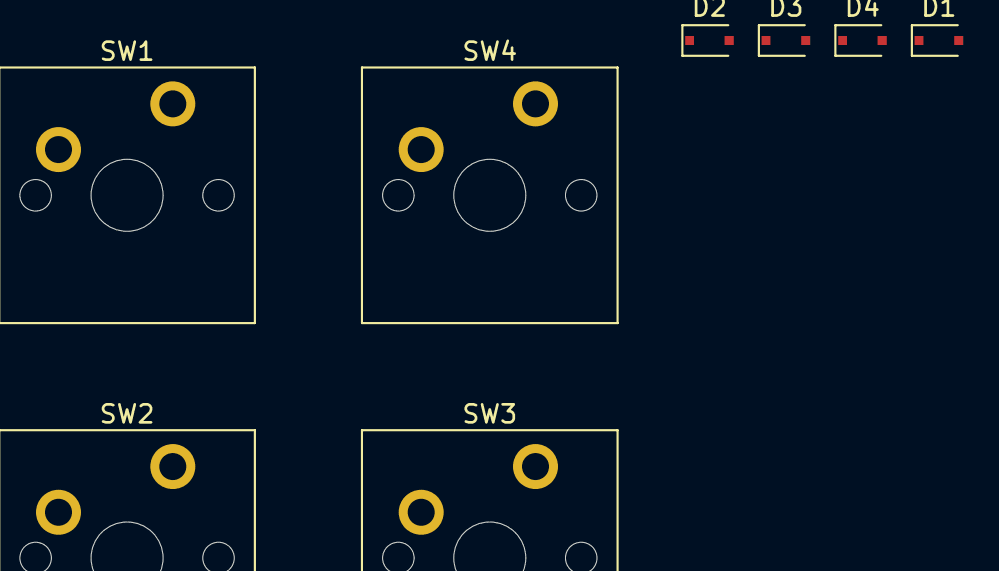
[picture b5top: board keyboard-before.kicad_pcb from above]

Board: 2 copper layers, 8 parts (0 on the bottom side), 7 nets, no tracks yet.

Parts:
D1, D2, D3, D4: D; D_SOD-323F
SW1, SW2, SW3, SW4: SW_Push; SW_Cherry_MX_PCB_1.00u

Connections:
COL0: SW1.1, SW2.1, SW3.1, SW4.1
unnamed: D1.2, SW1.2
unnamed: D2.1, SW2.2
unnamed: D3.2, SW3.2
unnamed: D4.1, SW4.2
ROW0: D1.1, D2.2
ROW1: D3.1, D4.2

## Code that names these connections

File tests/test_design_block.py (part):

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    def test_default_gpio_order(self) -> None:
        (preset,) = plan_presets([PresetSpec(MCU_V1)], _keyboard())
        assert preset.nets == {
            "GPIO0": "ROW0",
            "GPIO1": "ROW1",
            "GPIO2": "COL0",
            "GPIO3": "COL1",
        }
        assert preset.sheet_name == "mcu_atmega32u4_v1"

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            sheet_name="mcu",
            position=None,
            references={"U1": "U2", "BTN1": "BTN1"},
            nets={"GPIO0": "ROW0"},
        )
        assert preset.pcb_net_name("GPIO0") == "ROW0"
        assert preset.pcb_net_name("GPIO1") == "GPIO1"
        assert preset.pcb_net_name("Net-(U1-UCAP)") == "Net-(U2-UCAP)"
        assert (
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    assert aux_top > keyboard_bottom

    board_nets = _board_nets(board)
    # matrix connected to controller: PB0 (pad 8) is GPIO0 -> ROW0
    assert ("U1", "8") in board_nets["ROW0"]
    assert ("D1", "1") in board_nets["ROW0"]
    # internal nets of each preset are kept apart
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

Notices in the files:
tests/test_design_block.py:
SPDX-FileCopyrightText: 2026 adamws <adamws@users.noreply.github.com>
SPDX-License-Identifier: GPL-3.0-or-later
